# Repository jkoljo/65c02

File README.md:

# 65c02
Bits and pieces for a breadboard computer project

- 65c02 µboot, a small bootloader that provides a UI and xmodem-ish connectivity for loading apps to ram from a PC.

- 65c02 Teensy Master PCB, a level shifter to enable fast bidirectional communcation between Teensy 4.0 and the 65c02.

- J-Modem sender, a Python-based binary transfer app

- Teensy 65c02 coprocessor, a Teensy 4.0 program to emulate an ACIA, but much faster. With 912 MHz Teensy speed, it runs fast enough to reliably keep up with 1 MHz 65c02 clock and any amount of data throughput. Transfer speed with J-Modem sender is around 9000-10000 bytes/second.

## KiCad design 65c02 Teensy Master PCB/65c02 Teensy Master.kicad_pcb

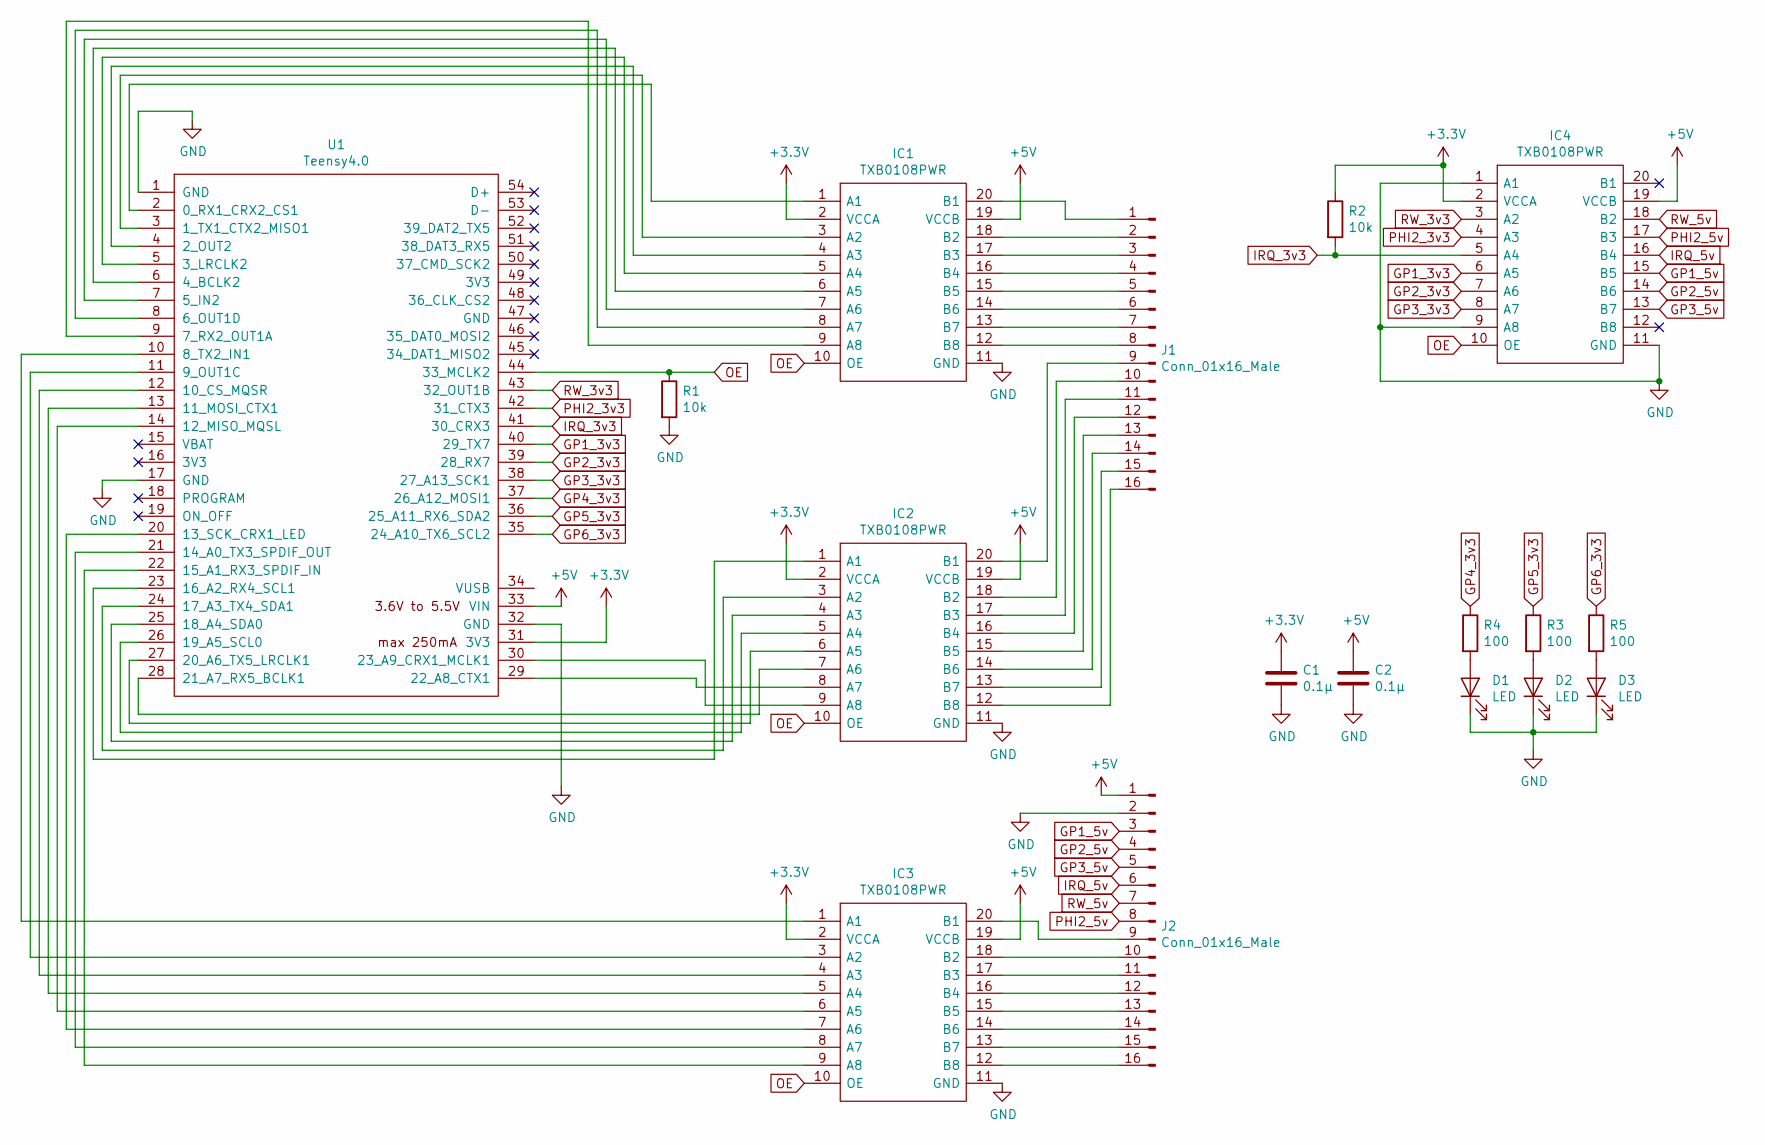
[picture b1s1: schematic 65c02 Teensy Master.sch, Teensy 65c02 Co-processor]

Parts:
C1, C2: 0.1µ; C_0805_2012Metric_Pad1.15x1.40mm_HandSolder
D1, D2, D3: LED; LED_0805_2012Metric_Pad1.15x1.40mm_HandSolder
IC1, IC2, IC3, IC4: TXB0108PWR; SOP65P640X120-20N; Mouser Part Number 595-TXB0108PWR
J1, J2: Conn_01x16_Male; PinHeader_1x16_P2.54mm_Vertical
R1, R2: 10k; R_0805_2012Metric_Pad1.15x1.40mm_HandSolder
R3, R4, R5: 100; R_0805_2012Metric_Pad1.15x1.40mm_HandSolder
U1: Teensy4.0; Teensy40

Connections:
+3V3: C1.1, IC1.2 (VCCA), IC2.2 (VCCA), IC3.2 (VCCA), IC4.2 (VCCA), R2.1, U1.31 (3V3)
+5V: C2.1, IC1.19 (VCCB), IC2.19 (VCCB), IC3.19 (VCCB), IC4.19 (VCCB), J2.1, U1.33 (VIN)
GND: C1.2, C2.2, D1.1 (K), D2.1 (K), D3.1 (K), IC1.11 (GND), IC2.11 (GND), IC3.11 (GND), IC4.1 (A1), IC4.9 (A8), IC4.11 (GND), J2.2, R1.2, U1.1 (GND), U1.17 (GND), U1.32 (GND)
GP1_3v3: IC4.6 (A5), U1.40 (29_TX7)
GP1_5v: IC4.15 (B5), J2.3
GP2_3v3: IC4.7 (A6), U1.39 (28_RX7)
GP2_5v: IC4.14 (B6), J2.4
GP3_3v3: IC4.8 (A7), U1.38 (27_A13_SCK1)
GP3_5v: IC4.13 (B7), J2.5
GP4_3v3: R4.1, U1.37 (26_A12_MOSI1)
GP5_3v3: R3.1, U1.36 (25_A11_RX6_SDA2)
GP6_3v3: R5.1, U1.35 (24_A10_TX6_SCL2)
IRQ_3v3: IC4.5 (A4), R2.2, U1.41 (30_CRX3)
IRQ_5v: IC4.16 (B4), J2.6
unnamed: D1.2 (A), R4.2
unnamed: D2.2 (A), R3.2
unnamed: D3.2 (A), R5.2
unnamed: IC1.1 (A1), U1.2 (0_RX1_CRX2_CS1)
unnamed: IC1.3 (A2), U1.3 (1_TX1_CTX2_MISO1)
unnamed: IC1.4 (A3), U1.4 (2_OUT2)
unnamed: IC1.5 (A4), U1.5 (3_LRCLK2)
unnamed: IC1.6 (A5), U1.6 (4_BCLK2)
unnamed: IC1.7 (A6), U1.7 (5_IN2)
unnamed: IC1.8 (A7), U1.8 (6_OUT1D)
unnamed: IC1.9 (A8), U1.9 (7_RX2_OUT1A)
unnamed: IC1.12 (B8), J1.8
unnamed: IC1.13 (B7), J1.7
unnamed: IC1.14 (B6), J1.6
unnamed: IC1.15 (B5), J1.5
unnamed: IC1.16 (B4), J1.4
unnamed: IC1.17 (B3), J1.3
unnamed: IC1.18 (B2), J1.2
unnamed: IC1.20 (B1), J1.1
unnamed: IC2.1 (A1), U1.23 (16_A2_RX4_SCL1)
unnamed: IC2.3 (A2), U1.24 (17_A3_TX4_SDA1)
unnamed: IC2.4 (A3), U1.25 (18_A4_SDA0)
unnamed: IC2.5 (A4), U1.26 (19_A5_SCL0)
unnamed: IC2.6 (A5), U1.27 (20_A6_TX5_LRCLK1)
unnamed: IC2.7 (A6), U1.28 (21_A7_RX5_BCLK1)
unnamed: IC2.8 (A7), U1.29 (22_A8_CTX1)
unnamed: IC2.9 (A8), U1.30 (23_A9_CRX1_MCLK1)
unnamed: IC2.12 (B8), J1.16
unnamed: IC2.13 (B7), J1.15
unnamed: IC2.14 (B6), J1.14
unnamed: IC2.15 (B5), J1.13
unnamed: IC2.16 (B4), J1.12
unnamed: IC2.17 (B3), J1.11
unnamed: IC2.18 (B2), J1.10
unnamed: IC2.20 (B1), J1.9
unnamed: IC3.1 (A1), U1.10 (8_TX2_IN1)
unnamed: IC3.3 (A2), U1.11 (9_OUT1C)
unnamed: IC3.4 (A3), U1.12 (10_CS_MQSR)
unnamed: IC3.5 (A4), U1.13 (11_MOSI_CTX1)
unnamed: IC3.6 (A5), U1.14 (12_MISO_MQSL)
unnamed: IC3.7 (A6), U1.20 (13_SCK_CRX1_LED)
unnamed: IC3.8 (A7), U1.21 (14_A0_TX3_SPDIF_OUT)
unnamed: IC3.9 (A8), U1.22 (15_A1_RX3_SPDIF_IN)
unnamed: IC3.12 (B8), J2.16
unnamed: IC3.13 (B7), J2.15
unnamed: IC3.14 (B6), J2.14
unnamed: IC3.15 (B5), J2.13
unnamed: IC3.16 (B4), J2.12
unnamed: IC3.17 (B3), J2.11
unnamed: IC3.18 (B2), J2.10
unnamed: IC3.20 (B1), J2.9
OE: IC1.10 (OE), IC2.10 (OE), IC3.10 (OE), IC4.10 (OE), R1.1, U1.44 (33_MCLK2)
PHI2_3v3: IC4.4 (A3), U1.42 (31_CTX3)
PHI2_5v: IC4.17 (B3), J2.8
RW_3v3: IC4.3 (A2), U1.43 (32_OUT1B)
RW_5v: IC4.18 (B2), J2.7

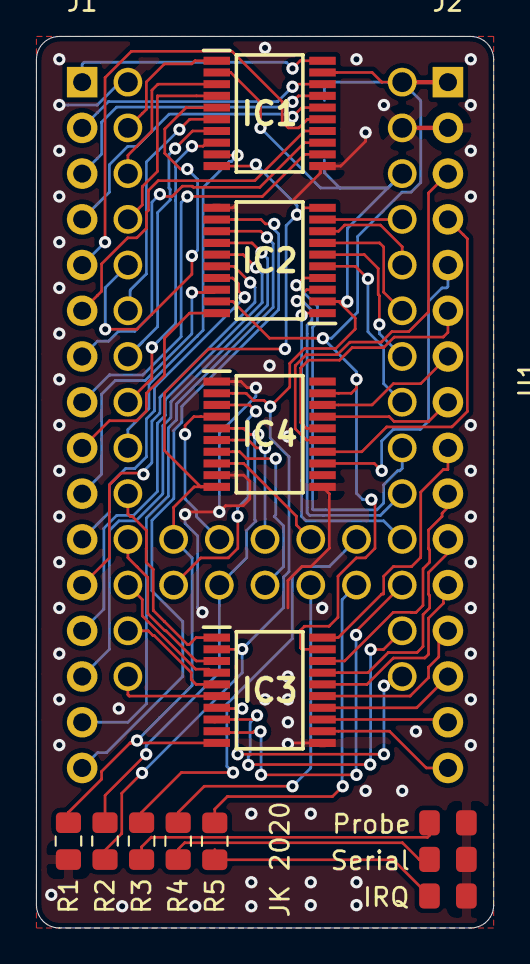
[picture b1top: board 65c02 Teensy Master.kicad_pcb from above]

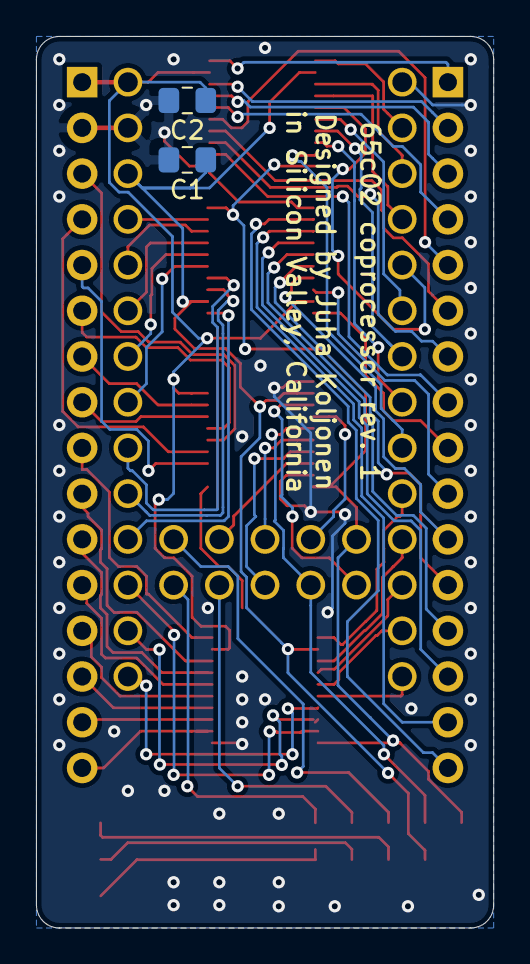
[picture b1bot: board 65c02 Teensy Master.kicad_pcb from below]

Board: 2 copper layers, 25.4 x 49.5 mm, 17 parts (2 on the bottom side), 70 nets.

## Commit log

2020-04-08 Add files
2020-04-08 More info to readme
2020-04-11 Add the beginnings of prog load via serial
2020-04-11 Update readme with JMODEM send app
2020-04-13 First usable version of load and run via serial
2020-04-13 Minor progress
2020-04-13 Checksum support and minor fixes
2020-04-14 Minor fixes
2020-04-14 Remove delays from sender. Update readme
2020-04-15 Improve decimal conversion functions
